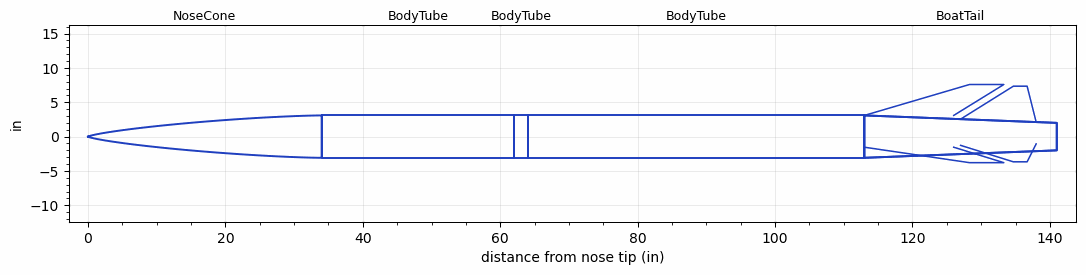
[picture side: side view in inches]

<RASAeroDocument>
 <FileVersion>2</FileVersion>
 <RocketDesign>
  <NoseCone>
   <Length>34</Length>
   <Diameter>6.17</Diameter>
   <Shape>Von Karman Ogive</Shape>
   <Location>0</Location>
  </NoseCone>
  <BodyTube>
   <Length>27.9999</Length>
   <Diameter>6.17</Diameter>
   <Location>34</Location>
  </BodyTube>
  <BodyTube>
   <Length>2</Length>
   <Diameter>6.17</Diameter>
   <Location>61.9999</Location>
  </BodyTube>
  <BodyTube>
   <Length>48.9999</Length>
   <Diameter>6.17</Diameter>
   <RailGuideDiameter>0.63</RailGuideDiameter>
   <RailGuideHeight>0.44</RailGuideHeight>
   <Location>63.9999</Location>
   <BoattailLength>27.9999</BoattailLength>
   <BoattailRearDiameter>4</BoattailRearDiameter>
   <Overhang>13</Overhang>
   <Fin>
    <Count>3</Count>
    <Chord>13</Chord>
    <Span>4.5</Span>
    <SweepDistance>15.2968</SweepDistance>
    <TipChord>5</TipChord>
    <Thickness>0.312</Thickness>
    <Location>0</Location>
    <AirfoilSection>Double Wedge</AirfoilSection>
    <FX1>1</FX1>
   </Fin>
  </BodyTube>
  <BoatTail>
   <Length>27.9999</Length>
   <Diameter>6.17</Diameter>
   <RearDiameter>4</RearDiameter>
   <Location>112.9998</Location>
   <Fin>
    <Count>3</Count>
    <Chord>11</Chord>
    <Span>4.8</Span>
    <SweepDistance>7.6837</SweepDistance>
    <TipChord>2</TipChord>
    <Thickness>0.312</Thickness>
    <Location>14</Location>
    <AirfoilSection>Double Wedge</AirfoilSection>
    <FX1>1</FX1>
   </Fin>
  </BoatTail>
  <Surface>Rough Camouflage Paint</Surface>
  <ModifiedBarrowman>False</ModifiedBarrowman>
  <Turbulence>False</Turbulence>
  <UseBooster1>False</UseBooster1>
  <UseBooster2>False</UseBooster2>
 </RocketDesign>
 <LaunchSite>
  <Altitude>3005</Altitude>
  <Pressure>29.89</Pressure>
  <RodAngle>6</RodAngle>
  <RodLength>17</RodLength>
  <Temperature>100</Temperature>
  <WindSpeed>10</WindSpeed>
 </LaunchSite>
 <Recovery>
  <Altitude1>656.168</Altitude1>
  <Altitude2>1500</Altitude2>
  <DeviceType1>Parachute</DeviceType1>
  <DeviceType2>Parachute</DeviceType2>
  <Event1>True</Event1>
  <Event2>True</Event2>
  <Size1>30</Size1>
  <Size2>144</Size2>
  <EventType1>Apogee</EventType1>
  <EventType2>Altitude</EventType2>
  <CD1>1.16</CD1>
  <CD2>2.2</CD2>
 </Recovery>
 <SimulationList>
  <Simulation>
   <SustainerEngine>O5500X  (AT)</SustainerEngine>
   <SustainerLaunchWt>89.15</SustainerLaunchWt>
   <SustainerNozzleDiameter>3.5</SustainerNozzleDiameter>
   <SustainerCG>91.75</SustainerCG>
   <SustainerIgnitionDelay>0</SustainerIgnitionDelay>
   <Booster1SeparationDelay>0</Booster1SeparationDelay>
   <Booster1IgnitionDelay>0</Booster1IgnitionDelay>
   <IncludeBooster1>False</IncludeBooster1>
   <Booster2Delay>0</Booster2Delay>
   <IncludeBooster2>False</IncludeBooster2>
   <TimetoApogee>36.68985</TimetoApogee>
   <MaxAltitude>24675.76</MaxAltitude>
   <MaxVelocity>1704.401</MaxVelocity>
   <OptimumWt>49.03252</OptimumWt>
   <OptimumMaxAlt>49.03252</OptimumMaxAlt>
  </Simulation>
  <Simulation>
   <SustainerLaunchWt>81.6884</SustainerLaunchWt>
   <SustainerCG>86.9013</SustainerCG>
   <SustainerIgnitionDelay>0</SustainerIgnitionDelay>
   <Booster1SeparationDelay>0</Booster1SeparationDelay>
   <Booster1IgnitionDelay>0</Booster1IgnitionDelay>
   <IncludeBooster1>False</IncludeBooster1>
   <Booster2Delay>0</Booster2Delay>
   <IncludeBooster2>False</IncludeBooster2>
  </Simulation>
  <Simulation>
   <SustainerLaunchWt>81.6884</SustainerLaunchWt>
   <SustainerCG>86.9013</SustainerCG>
   <SustainerIgnitionDelay>0</SustainerIgnitionDelay>
   <Booster1SeparationDelay>0</Booster1SeparationDelay>
   <Booster1IgnitionDelay>0</Booster1IgnitionDelay>
   <IncludeBooster1>False</IncludeBooster1>
   <Booster2Delay>0</Booster2Delay>
   <IncludeBooster2>False</IncludeBooster2>
  </Simulation>
  <Simulation>
   <SustainerLaunchWt>81.6884</SustainerLaunchWt>
   <SustainerCG>86.9013</SustainerCG>
   <SustainerIgnitionDelay>0</SustainerIgnitionDelay>
   <Booster1SeparationDelay>0</Booster1SeparationDelay>
   <Booster1IgnitionDelay>0</Booster1IgnitionDelay>
   <IncludeBooster1>False</IncludeBooster1>
   <Booster2Delay>0</Booster2Delay>
   <IncludeBooster2>False</IncludeBooster2>
  </Simulation>
  <Simulation>
   <SustainerLaunchWt>81.6884</SustainerLaunchWt>
   <SustainerCG>86.9013</SustainerCG>
   <SustainerIgnitionDelay>0</SustainerIgnitionDelay>
   <Booster1SeparationDelay>0</Booster1SeparationDelay>
   <Booster1IgnitionDelay>0</Booster1IgnitionDelay>
   <IncludeBooster1>False</IncludeBooster1>
   <Booster2Delay>0</Booster2Delay>
   <IncludeBooster2>False</IncludeBooster2>
  </Simulation>
  <Simulation>
   <SustainerLaunchWt>81.6884</SustainerLaunchWt>
   <SustainerCG>86.9013</SustainerCG>
   <SustainerIgnitionDelay>0</SustainerIgnitionDelay>
   <Booster1SeparationDelay>0</Booster1SeparationDelay>
   <Booster1IgnitionDelay>0</Booster1IgnitionDelay>
   <IncludeBooster1>False</IncludeBooster1>
   <Booster2Delay>0</Booster2Delay>
   <IncludeBooster2>False</IncludeBooster2>
  </Simulation>
 </SimulationList>
</RASAeroDocument>
